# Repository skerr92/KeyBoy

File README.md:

# KeyBoy
Home of all things KeyBoy - Games, board files, parts lists, and more!

### NOTICE ###
Licensed under MIT License, see LICENSE for details

### About ###
This repository holds all things for the KeyBoy. 

Currently we just have the EAGLE schematic and board files available, thoguh KiCAD files will be coming soon.

Additionally, the BOM and manufacturing files will be coming once with final design is validated.

Once you have hardware in hand, you will need to put the CircuitPython ESP32-S3 Mini Dev Kit image onto the ESP32-S3 onboard.

From there, copy over the required libraries listed in the code.py under the Firmware directory.

Copy `Firmware/Games/GameMenu.py` to `/lib` as well for the arcade
SEL pause menus. SEL opens Resume / Save / Leave; arcade games save high
scores and Lantern Acre saves its farm to `/lantern_acre.sav`.

The animated arcade launcher has a bevelled pixel logo, twinkling stars,
individual game emblems, and three pages of games. Up/Down selects; Left/Right
changes pages; A launches. Copy `Firmware/Games/KeyBoyLauncher.py` to
`/lib/KeyBoyLauncher.py` when updating `Firmware/code.py`.
The launcher releases its artwork and module before loading a game, then
rebuilds on return with the previous selection. Games are also unloaded on exit.
See [launcher previews and memory fixes](docs/launcher/README.md).

KeyBoy audio uses I2S enable `IO8` and BCLK/LRCLK/DATA pins `IO5`/`IO6`/`IO7`.
The dedicated SEL button is on `IO40`.
Copy `Firmware/Games/KeyBoyAudio.py` to `/lib` and the entire
`Firmware/Games/KeyBoySounds` folder to `/lib/KeyBoySounds`. The audio engine
streams distinct effects and musical cues through three independent voices,
with smooth envelopes and a continuous I2S stream to reduce clicks. See
[audio installation, sound tour, and validation](docs/audio/README.md).

Copy the code.py file to your CIRCUITPY drive and it should work.

The launcher now includes **Loose Cows**, **Sprite's Journey**, **Aerial Dog
Fight**, **Dungeons CYL**, **Lantern Acre**, **Wildspark**, **Ironbound**, and
**Last Beacon**, **Clockwork Courier**, and **Drift Circuit**.

The three arcade games now share `Firmware/Games/KeyBoyArcade.py`; copy it to
`/lib/KeyBoyArcade.py` alongside `GameMenu.py`. They use reusable 4-bit pixel
scenery and retained actors, with cached pause panels.

**Sprite's Journey** has nine collectible rooms, larger characters, guardian
projectiles, ranged magic, three hearts per room, and wings that enable gliding
from room four. Find every spark and defeat the guardian to open each gate.
A jumps (hold to glide), B fires magic, Left/Right moves. Copy its package to
`/lib/Sprites_Journey/`, including `Sprites_Journey.py` and `__init__.py`.

**Aerial Dog Fight** has larger aircraft over a coastal battlefield, twin/rapid
cannons, limited rechargeable boost, repair/loadout choices between sectors,
and a persistent ace with spread attacks. D-pad flies, A fires, B boosts.
Copy `Firmware/Games/Aerial Dog Fight/AerialDogFight.py` to `/lib/AerialDogFight.py`.

**Loose Cows** has illustrated ranch scenery, gold bonus cows, safer whistles,
lasso release, generous early deadlines, and ranch upgrades every three rounds.
A catches/releases, B whistles. Copy its package to `/lib/Loose_Cows/`.
All three support SEL pause and Up + Down to exit; existing best scores stay
compatible. See [arcade previews, controls, and verification](docs/arcade/README.md).

Dungeons CYL is a seven-floor pixel-art escape crawler with themed stonework,
larger animated characters, distinct guardians, torches, supply chests, and
telegraphed enemy attacks. D-pad walks, A swings the sword, hold B to guard,
and SEL pauses or retries the current floor. Defeat the guardian to open each
gate; cross spikes during their safe window. Six hearts, healing supplies,
and full-health floor retries keep the campaign recoverable.

The blocked guardian routes on floors 2 and 5 are repaired, and every floor
has automated start-to-guardian-to-exit completion coverage. Scenery and sprite
atlases stay allocated throughout play; opening a gate changes only its sprite.
Copy `Firmware/Games/Dungeons Can You Leave/Dungeons_CYL.py` to
`/lib/Dungeons_CYL.py`. Existing `/dungeons.txt` best scores remain compatible.
See [dungeon previews, controls, and validation](docs/dungeons/README.md).

Lantern Acre is a pixel-art homestead with an animated farmer, a furnished
cottage, six plots across the home farm and Lantern Meadow, four crop types,
and Lantern Market.
D-pad walks, A plants/waters/harvests the highlighted tile, B opens the market,
and SEL pauses. Approach the cottage door and press A to sleep, ship crops,
or check the farm journal. The chest beside the porch also ships your basket;
herbs beside the well provide $2 once per day if you run short of seed money.

A day lasts **four minutes of active farm time**; menus pause the clock.
Watered crops grow at dawn, and sleeping restores the **Season, Day X** morning
card before returning outside. Cross the east footbridge with A to reach the
meadow's three additional plots; buy plot unlocks at the market. The seed shop
offers named packets that grow year-round, seasonal discounts, and a planting
seed selector alongside the original mixed seeds.
Dry crops wait safely, ripe crops keep, and seasons change every eight days.
Crop prices differ; the copper can waters three adjacent crops and the cart
adds $1 per shipped crop. Sleep autosaves; SEL offers explicit save/leave
options and reports write failures (USB programming mode makes saves read-only).
Existing farm saves migrate automatically on the next successful save.

The terrain, sprite atlases, and crop TileGrids stay allocated during play.
Walking changes sprite positions; tending updates only affected tile indices;
menus reuse preallocated panels and labels over the retained farm, avoiding
large allocations when opening the store or pause menu. Dusk/night/dawn recolor the world palette
once per phase, without rebuilding the scene. No image files are needed.
Copy `Firmware/Games/Lantern_Acre/Lantern_Acre.py` to
`/lib/Lantern_Acre/Lantern_Acre.py` in the existing package to deploy it.
See [art previews and validation](docs/lantern-acre/README.md).

Wildspark is a pixel-art creature adventure with six detailed routes, an
animated trainer and traveling companion, and 27 large illustrated creature
forms. Recover relics, earn three sanctuary emblems, and challenge the rival.
Captured families become usable partners with individual HP, XP, and evolution.
Turn-based battles offer Strike, elemental Burst, Guard, Catch, Tonic, Switch,
Weaken, and Flee. Weaken leaves at least 1 HP; Catch succeeds at half HP or less.
All 27 forms can be found on later trails, and the guide provides habitat hints;
enemy intent makes charged attacks readable. Clinics heal the party and refill
supplies. D-pad moves, A interacts/confirms, B opens partners or retreats, and
SEL opens the pause/save/field-guide menu.

World and battle scenes retain their sprites between transitions, with small
bitmap strips and reusable menu panels. Legacy saves migrate to the expanded
party format at `/wildspark.sav`. Copy `Firmware/Games/Wildspark/Wildspark.py`
to `/lib/Wildspark/Wildspark.py` in the existing package. See
[Wildspark art, controls, and validation](docs/wildspark/README.md).

Ironbound is an eight-operation mech tactics campaign with an illustrated refit
bay, animated mechs, cannon/rail loadouts, visible enemy attack plans, and
permanent upgrade choices. Move off marked tiles, counterattack during enemy
recovery, use cover, and manage shield energy, repair kits, and EMP pulses.
Clear hostiles, activate relays or recover cargo, then extract. D-pad moves,
A targets/interacts, B guards, and SEL opens systems and checkpoint saves.

Every mission has legal-action completion coverage with both weapons and each
upgrade path. Scenes and menus retain their small bitmap strips and sprites.
Old `/ironbound.sav` saves migrate to the expanded checkpoint format. Copy
`Firmware/Games/Ironbound/Ironbound.py` to `/lib/Ironbound/Ironbound.py`. See
[Ironbound previews, controls, and validation](docs/ironbound/README.md).

Last Beacon is a sprite-based extraction shooter that starts aboard the
**L.B.S. Wayfarer**. Choose one of eight contracts and one of five weapons, including the new
autocannon and wide-spread breacher,
plus orbital/sentry/resupply/shield/stasis support before deploying. Complete salvage, hive
purge, or uplink objectives, reach the extraction pad to call your shuttle,
then board before its 12-second departure window closes. Each contract also
has a 100–150 second overall deadline; menus pause mission time.

Use D-pad to move and aim, hold A to fire and strafe, B to deploy support, and
SEL to pause. Empty magazines reload automatically; exhausted ammunition
switches to an emergency sidearm. Supply crates restore health/ammunition.
Successful extractions earn credits for armor and weapon refits aboard ship.

Last Beacon retains its terrain, enemies, projectiles and effects throughout
each mission. Only scene transitions replace the background. Copy
`Firmware/Games/Last_Beacon/Last_Beacon.py` to
`/lib/Last_Beacon/Last_Beacon.py` in the existing package. Career saves at
`/last_beacon.sav` migrate from the old campaign format; debrief attempts an
autosave, and ship services provide manual saving with failure feedback.
See [screenshots, controls and validation](docs/last-beacon/README.md).

**Clockwork Courier** adds twelve brass-and-steam delivery puzzles. Push every
power cell onto a dock, unlock the next workshop, and replay for efficiency
medals. D-pad walks/pushes, B undoes, and A or SEL opens the workshop with
restart/save/room selection. Every room is solvable; there is no timer or life
limit. See [Courier art, controls, and verification](docs/clockwork-courier/README.md).

**Drift Circuit** adds three themed racing circuits, three cars with different
handling, rechargeable boost, time records, and a three-race championship.
A accelerates, Left/Right steer, B brakes, Up boosts, Down recovers, and SEL
pauses. Ordered checkpoints prevent false laps; recovery keeps a stranded
car playable. See [racing art, controls, and verification](docs/drift-circuit/README.md).

Both additions use retained scenery, small sprite banks, and cached menu
panels. Copy `ClockworkCourier.py`, `DriftCircuit.py`, and `KeyBoyScenes.py`
from `Firmware/Games/` into `/lib/`, along with the updated launcher and
`code.py`. Their separate saves are `/clockwork.sav` and `/drift_circuit.sav`.
Up + Down exits either game. Existing games and saves remain compatible.

This uses a 1.3" ST7789 display which can be purchased from Adafruit.

### 3D Printed Case ###
Once I receive the next iteration of the board, I will be uploading a usable case here that can be printed on either resin or FDM 3D printers.
A CircuitPython board definition will be coming soon.

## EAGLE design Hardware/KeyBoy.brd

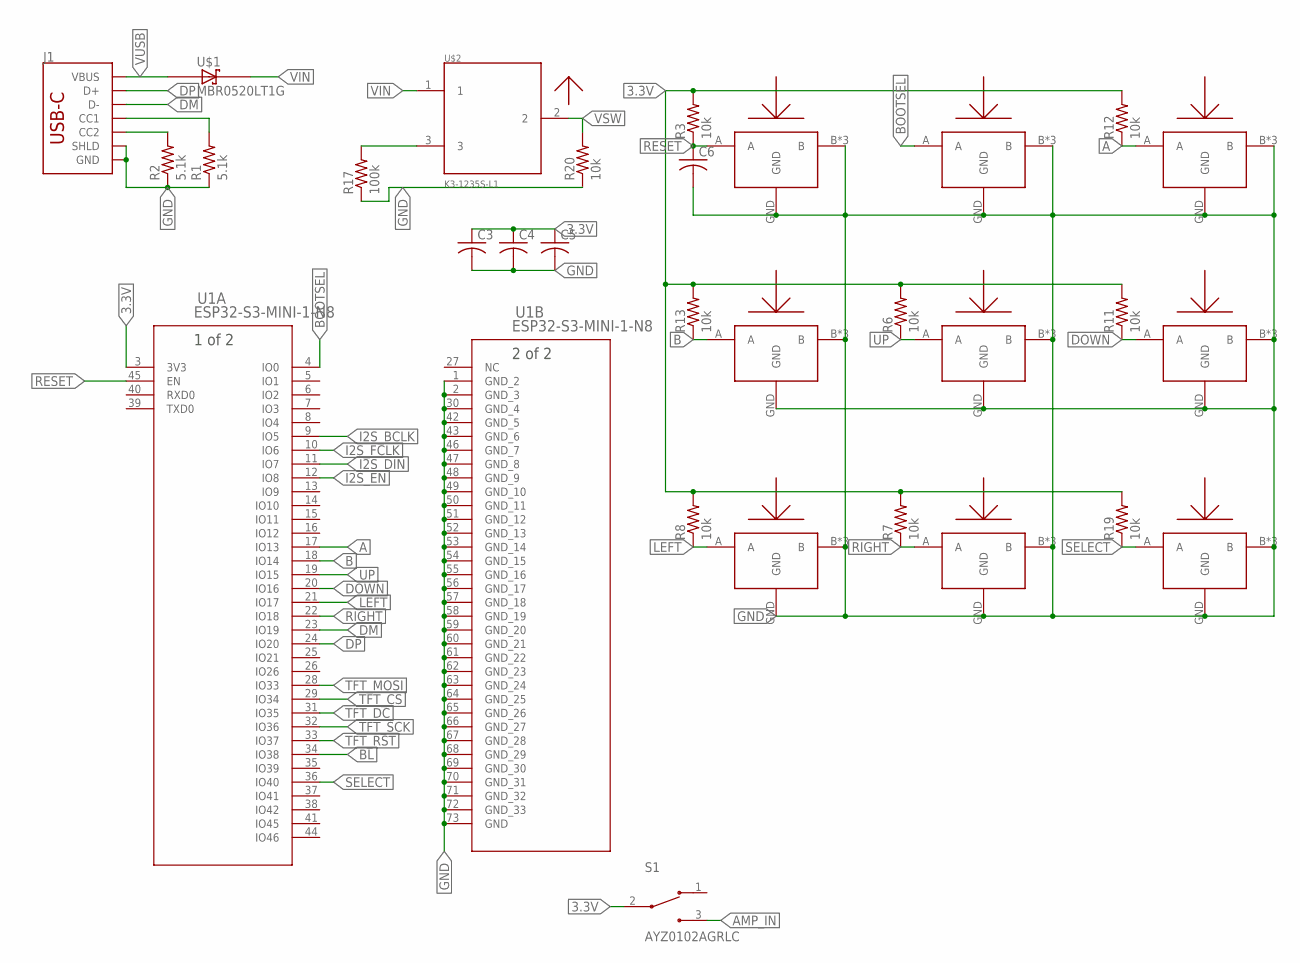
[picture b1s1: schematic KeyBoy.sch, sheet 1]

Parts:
A: SOF-232HST; 3.3X2.9
B: SOF-232HST; 3.3X2.9
BOOTSEL: SOF-232HST; 3.3X2.9
C3, C4, C5, C6: C-USC0402; C0402
DOWN: SOF-232HST; 3.3X2.9
J1: USB_C_2-LAYER_PADS; USB-C-16P-2LAYER-PADS
LEFT: SOF-232HST; 3.3X2.9
R1, R2: 5.1k; R0402
R3, R6, R7, R8, R11, R12, R13, R19, R20: 10k; R0402
R17: 100k; R0402
RESET: SOF-232HST; 3.3X2.9
RIGHT: SOF-232HST; 3.3X2.9
S1: AYZ0102AGRLC; SW_AYZ0102AGRLC
SELECT: SOF-232HST; 3.3X2.9
U1: ESP32-S3-MINI-1-N8; ESP32-S2-MINI-1-N4_EXP
U$1: MBR0520LT1G; SOD3716X117(SOD-123)
U$2: K3-1235S-L1
UP: SOF-232HST; 3.3X2.9

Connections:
3.3V: C3.1, C4.1, C5.1, R3.2, R6.2, R7.2, R8.2, R11.2, R12.2, R13.2, R19.2, S1.2, U1.3 (3V3); also elsewhere on the board
A: A.A, R12.1, U1.17 (IO13)
AMP_IN: S1.3; also elsewhere on the board
B: B.A, R13.1, U1.18 (IO14)
BL: U1.34 (IO38); also elsewhere on the board
BOOTSEL: BOOTSEL.A, U1.4 (IO0)
DM: J1.A7 (D-), J1.B7 (D-), U1.23 (IO19)
DOWN: DOWN.A, R11.1, U1.20 (IO16)
DP: J1.A6 (D+), J1.B6 (D+), U1.24 (IO20)
GND: A.B, A.B2 (B), A.B3 (B), A.GND, B.B, B.B2 (B), B.B3 (B), B.GND, BOOTSEL.B, BOOTSEL.B2 (B), BOOTSEL.B3 (B), BOOTSEL.GND, C3.2, C4.2, C5.2, C6.2, DOWN.B, DOWN.B2 (B), DOWN.B3 (B), DOWN.GND, J1.GND, J1.GND2 (GND), J1.P$1 (SHLD), J1.P$2 (SHLD), J1.P$3 (SHLD), J1.P$4 (SHLD), J1.SHLD1 (SHLD), J1.SHLD2 (SHLD), J1.SHLD3 (SHLD), J1.SHLD4 (SHLD), LEFT.B, LEFT.B2 (B), LEFT.B3 (B), LEFT.GND, R1.1, R2.1, R17.1, R20.1, RESET.B, RESET.B2 (B), RESET.B3 (B), RESET.GND, RIGHT.B, RIGHT.B2 (B), RIGHT.B3 (B), RIGHT.GND, SELECT.B, SELECT.B2 (B), SELECT.B3 (B), SELECT.GND, U1.1 (GND_2), U1.2 (GND_3), U1.30 (GND_4), U1.42 (GND_5), U1.43 (GND_6), U1.46 (GND_7), U1.47 (GND_8), U1.48 (GND_9), U1.49 (GND_10), U1.50 (GND_11), U1.51 (GND_12), U1.52 (GND_13), U1.53 (GND_14), U1.54 (GND_15), U1.55 (GND_16), U1.56 (GND_17), U1.57 (GND_18), U1.58 (GND_19), U1.59 (GND_20), U1.60 (GND_21), U1.61 (GND_22), U1.62 (GND_23), U1.63 (GND_24), U1.64 (GND_25), U1.65 (GND_26), U1.66 (GND_27), U1.67 (GND_28), U1.68 (GND_29), U1.69 (GND_30), U1.70 (GND_31), U1.71 (GND_32), U1.72 (GND_33), U1.73 (GND), UP.B, UP.B2 (B), UP.B3 (B), UP.GND; also elsewhere on the board
I2S_BCLK: U1.9 (IO5); also elsewhere on the board
I2S_DIN: U1.11 (IO7); also elsewhere on the board
I2S_EN: U1.12 (IO8); also elsewhere on the board
I2S_FCLK: U1.10 (IO6); also elsewhere on the board
LEFT: LEFT.A, R8.1, U1.21 (IO17)
unnamed: J1.A5 (CC1), R1.2
unnamed: J1.B5 (CC2), R2.2
unnamed: R17.2, U$2.3
RESET: C6.1, R3.1, RESET.A, U1.45 (EN)
RIGHT: R7.1, RIGHT.A, U1.22 (IO18)
SELECT: R19.1, SELECT.A, U1.36 (IO40)
TFT_CS: U1.29 (IO34); also elsewhere on the board
TFT_DC: U1.31 (IO35); also elsewhere on the board
TFT_MOSI: U1.28 (IO33); also elsewhere on the board
TFT_RST: U1.33 (IO37); also elsewhere on the board
TFT_SCK: U1.32 (IO36); also elsewhere on the board
UP: R6.1, U1.19 (IO15), UP.A
VIN: U$1.1 (C), U$2.1; also elsewhere on the board
VSW: R20.2, U$2.2; also elsewhere on the board
VUSB: J1.VBUS1 (VBUS), J1.VBUS2 (VBUS), U$1.2 (A); also elsewhere on the board

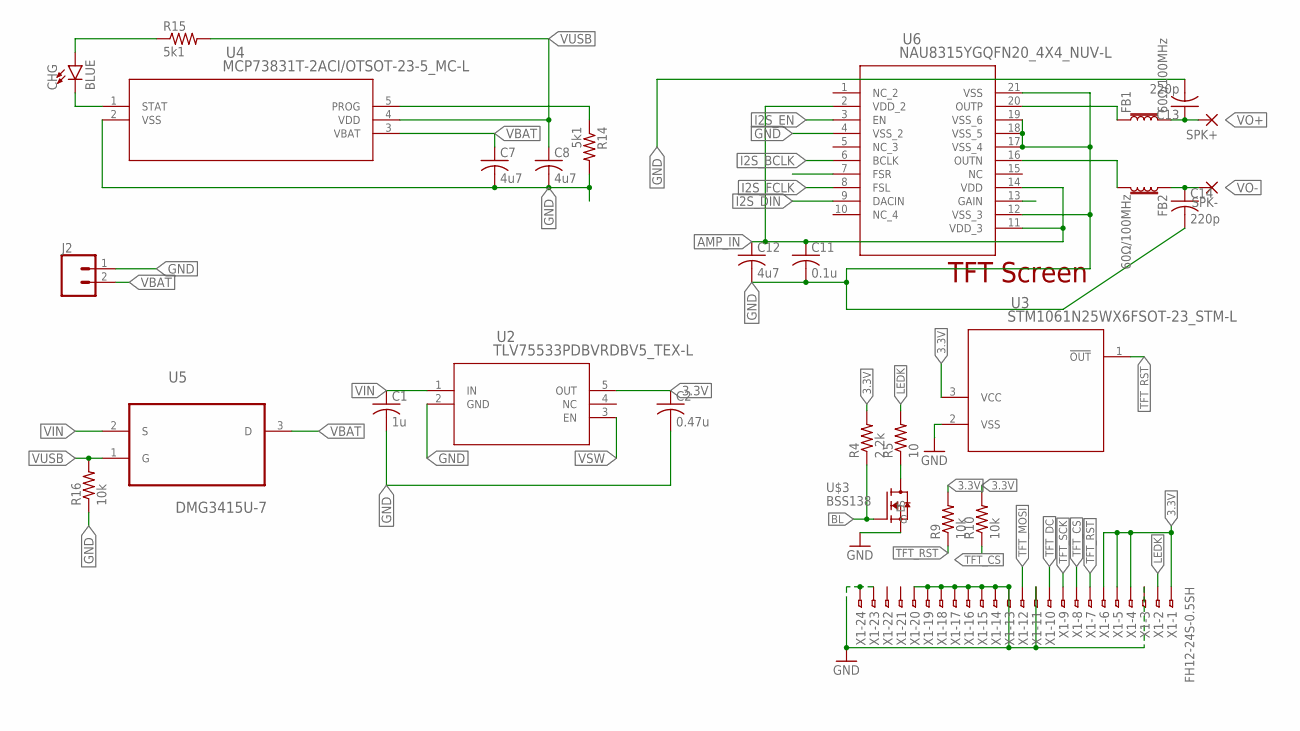
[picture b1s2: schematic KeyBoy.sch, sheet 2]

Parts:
C1: 1u; C0402
C2: 0.47u; C0402
C7, C8, C12: 4u7; C0603
C11: 0.1u; C0603
C13, C14: 220p; C0603
CHG: BLUE; LED-0603
FB1, FB2: 60Ω/100MHz; 0603
J2: CONN_02-JST-2MM-SMT; JST-2-SMD
R4: 2.2k; R0603
R5: 10; R0402
R9, R10, R16: 10k; R0402
R14, R15: 5k1; R0603
SPK+: SMD5; SMD2,54-5,08
SPK-: SMD5; SMD2,54-5,08
U2: TLV75533PDBVRDBV5_TEX-L; DBV5_TEX-L
U3: STM1061N25WX6FSOT-23_STM-L; SOT-23_STM-L
U4: MCP73831T-2ACI/OTSOT-23-5_MC-L; SOT-23-5_MC-L
U5: DMG3415U-7; SOT95P240X105-3N
U6: NAU8315YGQFN20_4X4_NUV-L; QFN20_4X4_NUV-L
U$3: BSS138
X1: FH12-24S-0.5SH

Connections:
3.3V: C2.1, R4.2, R9.2, R10.2, U2.5 (OUT), U3.3 (VCC), X1.1, X1.4, X1.5, X1.6; also elsewhere on the board
AMP_IN: C11.1, C12.1, U6.2 (VDD_2), U6.11 (VDD_3), U6.14 (VDD); also elsewhere on the board
BL: R4.1, U$3.G; also elsewhere on the board
GND: C1.2, C2.2, C7.2, C8.2, C11.2, C12.2, C13.2, C14.2, J2.1 (2), R14.2, R16.1, U2.2 (GND), U3.2 (VSS), U4.2 (VSS), U6.4 (VSS_2), U6.12 (VSS_3), U6.17 (VSS_4), U6.18 (VSS_5), U6.19 (VSS_6), U6.21 (VSS), U$3.S, X1.3, X1.11, X1.13, X1.14, X1.15, X1.16, X1.17, X1.18, X1.19, X1.20, X1.23, X1.24; also elsewhere on the board
I2S_BCLK: U6.6 (BCLK); also elsewhere on the board
I2S_DIN: U6.9 (DACIN); also elsewhere on the board
I2S_EN: U6.3 (EN); also elsewhere on the board
I2S_FCLK: U6.8 (FSL); also elsewhere on the board
LEDK: R5.2, X1.2
unnamed: R14.1, U4.5 (PROG)
unnamed: FB1.1, U6.20 (OUTP)
unnamed: R5.1, U$3.D
unnamed: FB2.2, U6.16 (OUTN)
unnamed: CHG.C, U4.1 (STAT)
unnamed: CHG.A, R15.1
TFT_CS: R10.1, X1.8; also elsewhere on the board
TFT_DC: X1.10; also elsewhere on the board
TFT_MOSI: X1.12; also elsewhere on the board
TFT_RST: R9.1, U3.1 (!OUT), X1.7; also elsewhere on the board
TFT_SCK: X1.9; also elsewhere on the board
VBAT: C7.1, J2.2 (1), U4.3 (VBAT), U5.3 (D)
VIN: C1.1, U2.1 (IN), U5.2 (S); also elsewhere on the board
VO+: C13.1, FB1.2, SPK+.1
VO-: C14.1, FB2.1, SPK-.1
VSW: U2.3 (EN); also elsewhere on the board
VUSB: C8.1, R15.2, R16.2, U4.4 (VDD), U5.1 (G); also elsewhere on the board

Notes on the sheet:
TFT Screen

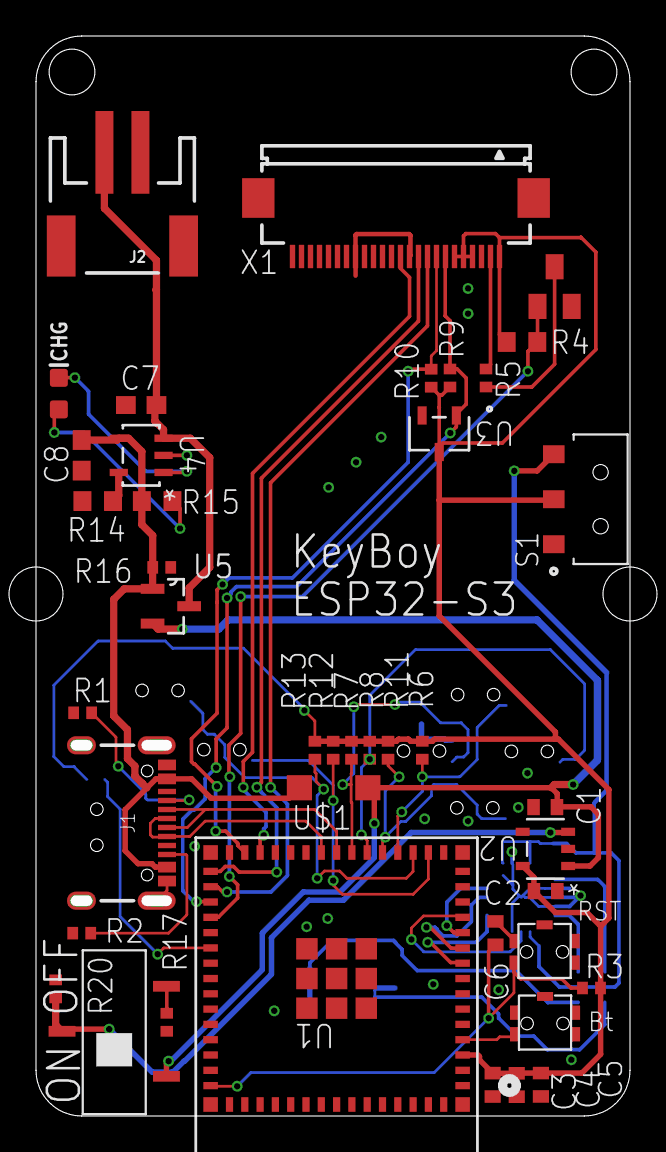
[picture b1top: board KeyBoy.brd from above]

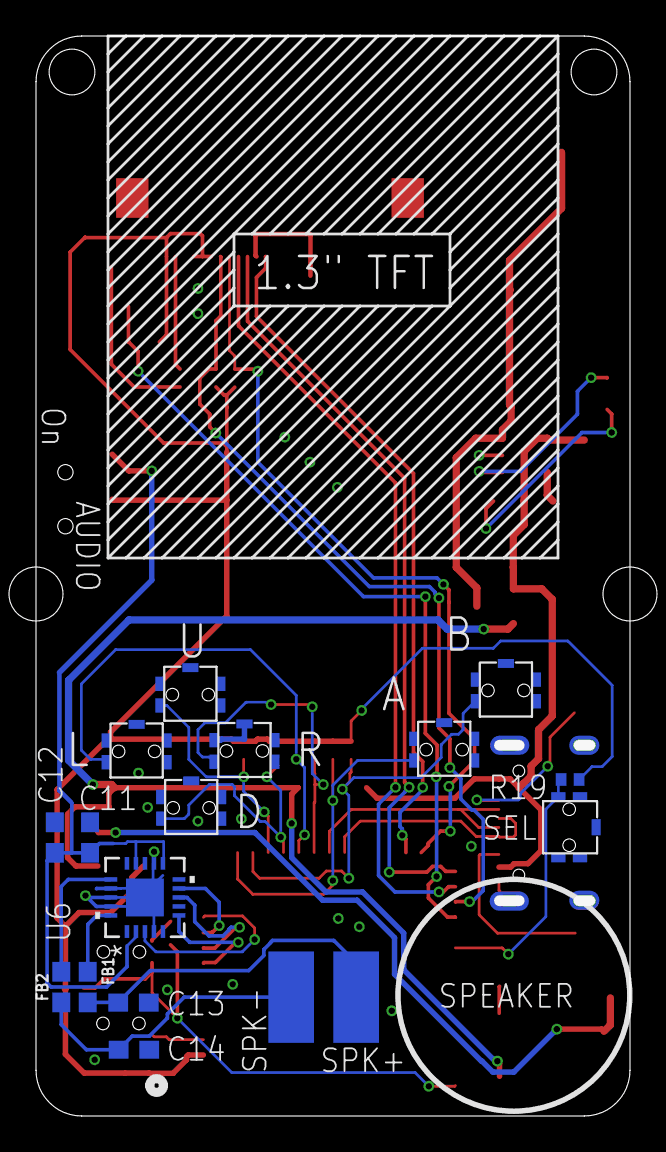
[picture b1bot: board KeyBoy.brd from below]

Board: 2 copper layers, 33.0 x 60.0 mm, 58 parts (17 on the bottom side), 40 nets.

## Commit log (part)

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2023-10-12 Adding basic files and updating readme
2023-10-14 updating game and structure
2023-10-15 Add schematics and brd files
2023-12-04 fixing bugs
    1. fix bug with timer running out after 50 cows caught
    2. fixing main code.py
    3. added the start of two additional games
2023-12-09 updating hardware files

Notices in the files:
parts and their libraries:
SparkFun-Connectors: Licensing: Creative Commons ShareAlike 4.0 International - https://creativecommons.org/licenses/by-sa/4.0
COPYRIGHT: Copyright (C) 2021 Ultra Librarian. All rights reserved.
COPYRIGHT: Copyright (C) 2018 Accelerated Designs. All rights reserved
